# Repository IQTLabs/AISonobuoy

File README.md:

[contributors-shield]: https://img.shields.io/github/contributors/IQTLabs/edgetech-audio-recorder.svg?style=for-the-badge
[contributors-url]: https://github.com/IQTLabs/edgetech-audio-recorder/graphs/contributors
[forks-shield]: https://img.shields.io/github/forks/IQTLabs/edgetech-audio-recorder.svg?style=for-the-badge
[forks-url]: https://github.com/IQTLabs/edgetech-audio-recorder/network/members
[stars-shield]: https://img.shields.io/github/stars/IQTLabs/edgetech-audio-recorder.svg?style=for-the-badge
[stars-url]: https://github.com/IQTLabs/edgetech-audio-recorder/stargazers
[issues-shield]: https://img.shields.io/github/issues/IQTLabs/edgetech-audio-recorder.svg?style=for-the-badge
[issues-url]: https://github.com/IQTLabs/edgetech-audio-recorder/issues
[license-shield]: https://img.shields.io/github/license/IQTLabs/edgetech-audio-recorder.svg?style=for-the-badge
[license-url]: https://github.com/IQTLabs/edgetech-audio-recorder/blob/master/LICENSE.txt
[product-screenshot]: images/screenshot.png

[Python]: https://img.shields.io/badge/python-000000?style=for-the-badge&logo=python
[Python-url]: https://www.python.org
[Poetry]: https://img.shields.io/badge/poetry-20232A?style=for-the-badge&logo=poetry
[Poetry-url]: https://python-poetry.org
[Docker]: https://img.shields.io/badge/docker-35495E?style=for-the-badge&logo=docker
[Docker-url]: https://www.docker.com

[![Contributors][contributors-shield]][contributors-url]
[![Forks][forks-shield]][forks-url]
[![Stargazers][stars-shield]][stars-url]
[![Issues][issues-shield]][issues-url]
[![MIT License][license-shield]][license-url]

<br />
<div align="center">

<h1 align="center">AISonobuoy</h1>

  <p align="center"> 
    <br/>
    <br/>
    <a href="https://github.com/IQTLabs/AISonobuoy/pulls">Make Contribution</a>
    ·
    <a href="https://github.com/IQTLabs/AISonobuoy/issues">Report Bug</a>
    ·
    <a href="https://github.com/IQTLabs/AISonobuoy/issues">Request Feature</a>
  </p>
</div>

## About

## Getting Started

## Software

### Running

#### Prerequisites

## Machine Learning

### Running

#### Prerequisites

### Development

## Hardware

### BOM

### 3D Printed STL Files

### Assembly Animation (Coming soon...)

## Roadmap

## Contributing

1. Fork the Project
2. Create your Feature Branch (`git checkout -b dev`)
3. Commit your Changes (`git commit -m 'adding some feature'`)
5. Push to the Branch (`git push origin dev`)
6. Open a Pull Request

See `CONTRIBUTING.md` for more information.

## License

Distributed under the [Apache 2.0](https://github.com/IQTLabs/aisonobuoy-collector-pinephone/blob/main/LICENSE). See `LICENSE` for more information.

## Contact IQTLabs

  - Twtiter: [@iqtlabs](https://twitter.com/iqtlabs)
  - Email: info@iqtlabs.org

See our other projects: [https://github.com/IQTLabs/](https://github.com/IQTLabs/)

<p align="right">(<a href="#readme-top">back to top</a>)</p>

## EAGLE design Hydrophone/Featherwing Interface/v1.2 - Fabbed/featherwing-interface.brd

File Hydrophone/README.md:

# TinyML & Hydrophones

## What are these things?

This is a small effort to look at running ML models against Hydrophone data on an Arduino or similar microcontroller. TinyML focuses on getting machine learning working on these lower power devices. New tools, like [Edge Impulse](https://www.edgeimpulse.com), have made it easy to start building your own ML models. 

Hydrophones are microphones that can capture underwater sounds. You will often see them in movies where they are hunting submarines. There are lots of interesting things you can hear underwater, like fish, volcanos and boats. 

Being able to push audio from a hydrophone through a TinyML model would make it possible to build a self-contained sensor that could detect underwater events.

## What is this?

This work was put together to see if it is possible to detect underwater events on an Arduino. It includes a board for connecting a hydrophone to a microntroller and a small Arduino program that runs an ML model and displays whether a boat was detected.

### Hydrophone Interface Board

This is a Featherwing form factor board that has a 3.5mm jack, a MAX4466 chip and adjustable gain. It outputs the amplified audio out on one of the Feather analog pinouts. There is a short step-by-step walk through on how I built the board on [Hackster.io](https://www.hackster.io/robotastic/hydrophone-feather-board-03f1d7).

I used the following parts. I am not an EE, so feel free to pick more appropriate components (and send me a PR if you do!):
- [Adafruit PyBadge](https://www.adafruit.com/product/4200)
- [Capacitor 0.01uF / 10000pF 0805](https://www.digikey.com/en/products/detail/CL21C103JBFNNNG/1276-6487-1-ND/5958115?itemSeq=376128529)
- [Capacitor 10uF 0805](https://www.digikey.com/short/m8wb1vc5)
- [Capacitor 100pF 0805](https://www.digikey.com/short/bvph8r4p)
- [Capacitor 0.1uF 0805](https://www.digikey.com/short/ftrt382h)
- [Ferrite Bead 0805](https://www.digikey.com/short/7c5j278m)
- [3.5mm Monojack](https://www.digikey.com/short/59mz8349)
- [Resistor 1k ohm 0805](https://www.digikey.com/short/q990d7bq)
- [Resistor 1M ohm 0805](https://www.digikey.com/short/53rz9h3m)
- [Resistor 22K ohm 0805](https://www.digikey.com/short/hj1djmt8)
- [MAX4466EXK+T  SC-70-5](https://www.digikey.com/short/vnww7j39)
- [Featherwing Male Headers](https://www.adafruit.com/product/3002) 

Here is a short journey on how the board came to be:

I selected the Aquarian hydrophone to work with. The [H2A model](https://www.aquarianaudio.com/h2a-hydrophone.html) seemed to be rugged and reasonably priced, for a hydrophone. It uses a standard 3.5mm jack, making it easy to connect to a lot of different recorders. 

I haven't worked much with microphones before, so I learned a number of things. First, microphones need a bit of power to work, so they will not work on a "line-in" input. For interfacing with an Arduino, this means that you can not simply hook it up to a GPIO pin and read the signal. You need to put some power through the microphone. Secondly, the actual signal from a microphone is quite faints and needs to be amplified before you can start to work with. 

The good news is that there are lots of existing chips for working with microphones that handle both the power and the gain. The surprising thing though, was that I couldn't find an existing board that had a 3.5mm jack and was designed to be connected to an Arduino. In fact, there wasn't really that much information about recording analog audio, directly from a microphone using Arduino. Most of the microphone breakout boards I found were for MEMS style microphones and most of them put out a digital signal. 

Adafruit does have a nice [breakout board](https://www.adafruit.com/product/1063) that uses a MAX4466 chip to power and amplify a Electret  Microphone. This is a similar type of microphone as the one inside the hydrophone. Adafruit also published a nice [guide](https://learn.adafruit.com/tensorflow-lite-for-edgebadge-kit-quickstart/assembly) on how to connect this microphone to one of their [dev boards](https://www.adafruit.com/product/4200) and how to run a TinyML model against that audio. Sampling the audio is a bit of a brute force approach - you simply set an interrupt and sample the pin at a set interval. As a quick experiment, I removed the microphone from the breakout board, added a 3.5mm jack and was able to record audio from the hydrophone.

One of the great things about Adafruit is that they open source all of their hardware designs. I started with the design files for the Electret Mic Breakout Board, moved them around to fit inside the feather form factor and added a 3.5mm jack.

The resulting board fits nicely on the back of the PyBadge and will work with the large range of dev boards that are in the Feather form factor.

Unfortunately, the audio from the interface board is not as high quality as audio recorded from a digital recorder (Zoom H1n). In order to evaluate performance I used an underwater speaker to playback an audio clip. I placed both the microphone and hydrophone in bucket, to try and make it a little more realistic. 

- [Interface Board](media/FeatherWing-Audio-Test.wav)
- [Digital Recorder](media/Digital-Recorder.wav)

As you can hear, the audio recorded by the interface board is a little more muffled and has more noise than the audio recorded by the digital recorder. (It is a little jumpy because it is recorded in 1 second segments.)

The difference maybe from the sampling technique used to capture the audio, it is only 12-bits. It is more likely from the design of the interface board. Cleaning amplifying audio is an art... and I am not an artist. Any improvements to the design of the interface board would be greatly appreciated.

### Arduino Program

The Arduino program builds off of the example Arduino program from Edge Impulse for inferencing. It is designed to run on the Adafruit [Pybadge](https://www.adafruit.com/product/4200) or Edge Badge. These are a series of development boards with a SAMD51 Cortex M4F processor and a small TFT LCD screen. 

The example program is written to pull audio from a PDM microphone. I updated it to instead sample from an analog pin. The results of running the model on the audio are displayed on the screen, along with the waveform of the audio. It makes for a compact kit for debugging and evaluating model performance in the field.

## Building an ML Based Boat Detector

Generally, the first step in building an ML model is to collect data and label it. For boat detection, I wanted recordings where there was a boat going by in the water and also recordings where there are no boats present. I captured the recordings using a [Zoom H1n recorder](https://zoomcorp.com/en/us/handheld-recorders/handheld-recorders/h1n-handy-recorder/) and the Acquarian hydrophone. In addition to not being an audio expert, I am also not a boating expert. I learned a couple lessons about boats by trying to make these recordings:

1. Just because a boat is docked and not moving, doesn't mean that it is making boat sounds. It turns out that a pump and maybe a motor will be running even if the boat is docked. This means that it is a bad idea to try and record near a marina, because there will be a lot of background boat sounds, even if nothing is moving nearby.
1. Boats can sound very different. The diesel engine on the water taxi sounds a lot different that the outboard engine on a power boat.

I uploaded the different recordings to Edge Impulse and trained a model. They have recently added an AutoML feature to the platform and using that I was able to train a model that almost perfectly classified each type of audio. This is encouraging, but also suggests that I may need more audio and more variety.

## Results 
I did some field evaluation and the system is able to detect nearby boats. More testing is need to see how it would perform in different bodies of water besides a river. Additional training data should help improve performance and allow the model to generalize to a broader range of boats and conditions. Improvements to the interface board should also improve performance.

An Arduino library that includes this model is included. I will look to added the recorded audio to the repo in the future.

## Contact

If you have questions or advice, please reach out to me (Luke Berndt) -> lberndt@iqt.org

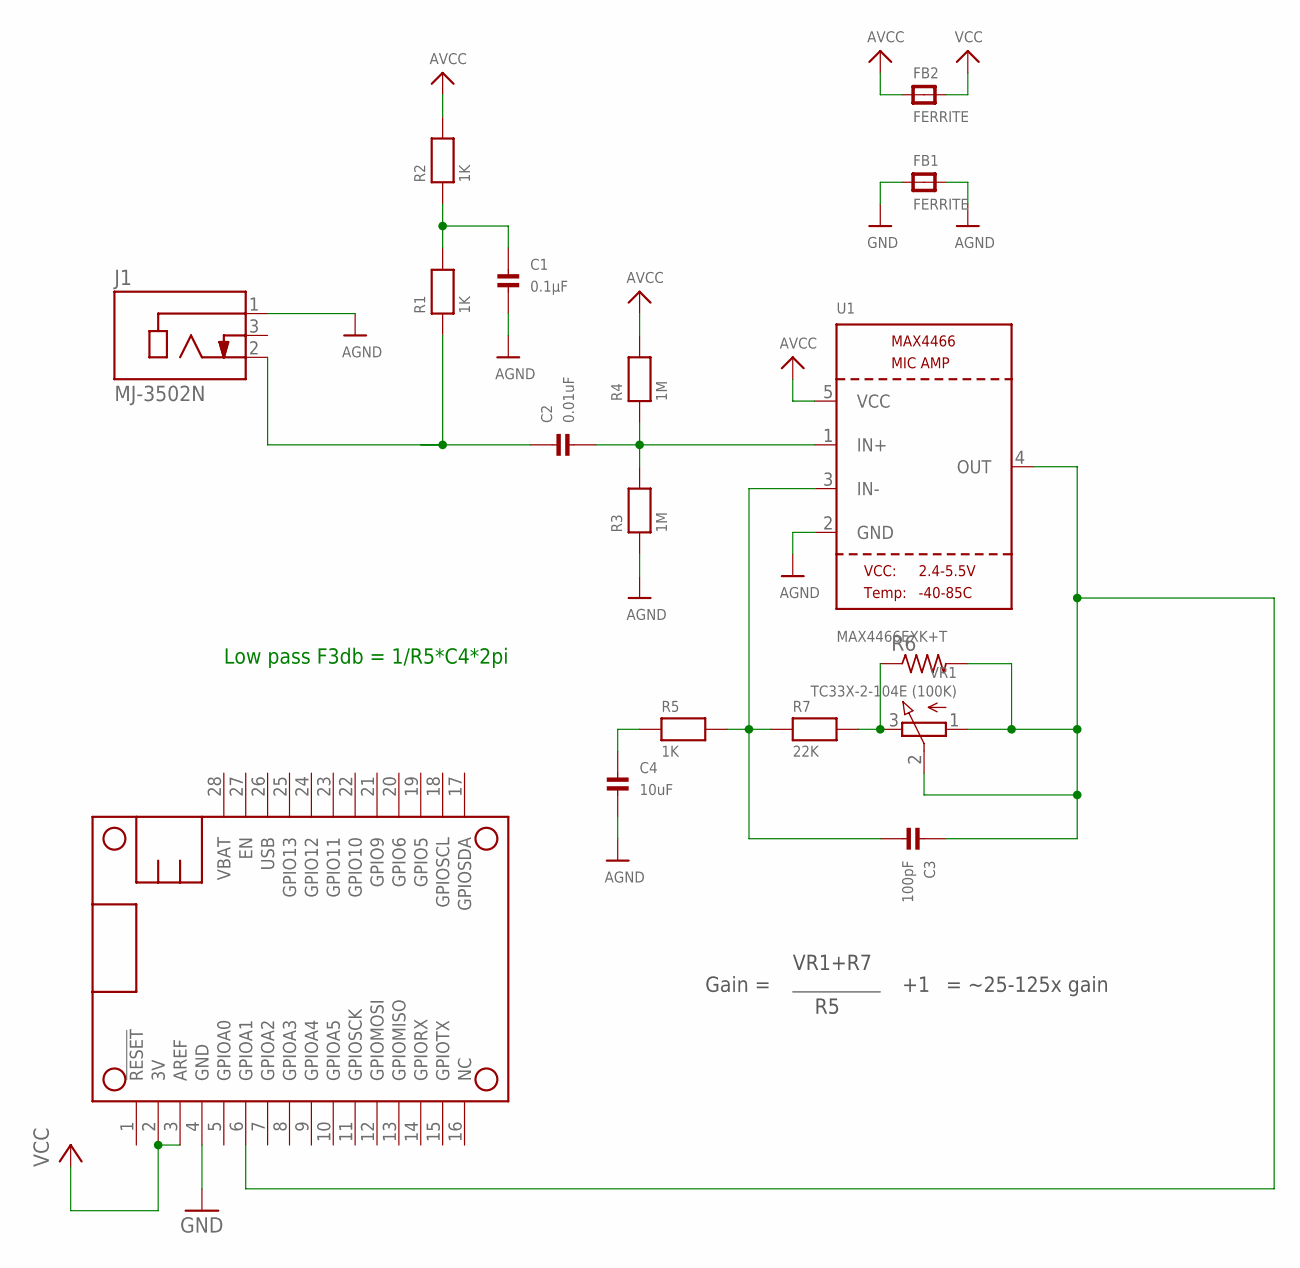
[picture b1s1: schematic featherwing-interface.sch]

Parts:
C1: 0.1µF; 0805
C2: 0.01uF; 0805
C3: 100pF; 0805
C4: 10uF; 0805
FB1, FB2: FERRITE; 0805
J1: MJ-3502N; CUI_MJ-3502N
MS1: FEATHERWING
R1, R2, R5: 1K; 0805
R3, R4: 1M; 0805
R6: R-US_0207/10; 0207/10
R7: 22K; 0805
U1: MAX4466EXK+T; SC70-5
VR1: TC33X-2-104E (100K); TRIMPOT_BOURNS_TC33X-2

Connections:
AGND: C1.2, C4.2, FB1.2, J1.1, R3.1, U1.2 (GND)
AVCC: FB2.1, R2.2, R4.2, U1.5 (VCC)
GND: FB1.1, MS1.4 (GND)
unnamed: C3.2, R5.2, R7.1, U1.3 (IN-)
unnamed: R6.1, R7.2, VR1.3 (E)
unnamed: C2.1, J1.2, R1.1
unnamed: C1.1, R1.2, R2.1
unnamed: C2.2, R3.2, R4.1, U1.1 (IN+)
unnamed: C3.1, MS1.6 (GPIOA1), R6.2, U1.4 (OUT), VR1.1 (A), VR1.2 (S)
unnamed: C4.1, R5.1
VCC: FB2.2, MS1.2 (3V), MS1.3 (AREF)

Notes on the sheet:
Gain =
VR1+R7
= ~25-125x gain
Low pass F3db = 1/R5*C4*2pi

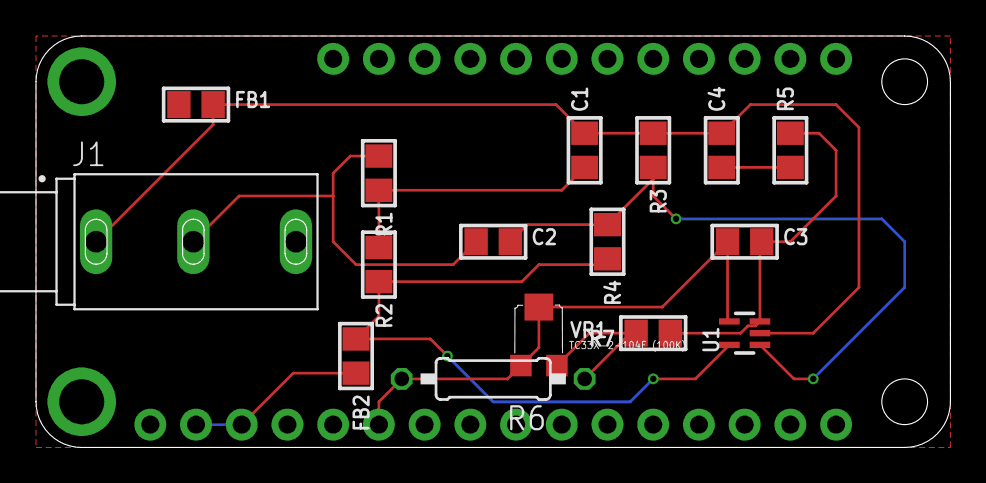
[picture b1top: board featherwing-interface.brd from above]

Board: 2 copper layers, 50.8 x 22.9 mm, 17 parts (0 on the bottom side), 11 nets.

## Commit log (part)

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2022-07-06 Upgrade requirements
2022-07-06 Update actions/checkout action to v3
2022-07-11 Create and use split_parquet method for testing
2022-07-11 Add ais-fixed.parquet
2022-07-11 Change type on test fixture
2022-07-12 Remove a test as a test
2022-07-12 Remove augmented fields as a test
2022-07-12 Testing only integers as a test
2022-07-12 Compare distance and speed to within a threshold
2022-07-12 Change float comparison to relative from absolute
2022-07-12 Minor comment change
2022-07-12 Attempt to resolve static code analysis issues
2022-07-12 Resolve static code analysis issues
2022-07-12 Try yet again to resolve static code analysis issue
2022-07-12 Remove bandit configuration since it is set on the codacy side
2022-07-13 Update test and add DataScience workflow (#854)
    * Add workflow and fix test paths
    * Upgrade requirements
    * Upgrade requirements
    * Upgrade requirements
    * Create and use split_parquet method for testing
    * Update test workflow
2022-07-14 Update dependency pyais to v2
2022-07-15 Update actions/setup-python action to v4
2022-07-18 Refresh pip-compile outputs
2022-07-18 Update boto packages
2022-07-20 Fix pyais version
2022-07-20 Add a package rule (#879)
    * Update dependency jsonschema to v4.7.2
    * Update dependency nbclassic to v0.4.3
    * Update dependency zipp to v3.8.1
    * Update dependency pyais to v2
    * Update dependency awscli to v1.25.30
    * Update dependency boto3 to v1.24.30
2022-07-22 Update dependency awscli to v1.25.35 (#882)
2022-07-25 updated graphing code
2022-07-25 codacy formatting cleanup
2022-07-27 Update Update dependency botocore and boto3
2022-07-28 Update group name for boto package rule
2022-07-29 formatting 2
2022-07-29 cleanup
2022-08-02 Update dependency attrs to v22
2022-08-11 Update dependency pyarrow to v9
2022-08-12 Update dependency mistune to v2 [SECURITY]
2022-08-31 Update dependency docker to v6
2022-08-31 fix more paths for pytype
2022-08-31 comment edits
2022-09-01 revised testing scripts
2022-09-01 missed a zero length test
2022-09-02 review revisions
2022-09-22 Update actions/stale action to v6
2022-09-28 inital torch modeling pipeline + cleanup
2022-10-02 training loop + minor edits
2022-10-04 documentation v1
2022-10-05 Correct spelling errors
2022-10-06 add torch -> ONNX -> keras -> tflite conversion
2022-10-06 fix semgrep Python errors
2022-10-11 adding clustering pipeline
2022-10-14 rnd 1 codacity updates
2022-10-14 rnd 2 codacity updates
2022-10-14 rnd 4 codacity updates
2022-10-17 codacity rnd 5
2022-10-17 adding clustering scripts
2022-10-17 renaming directory
2022-10-17 codacity rnd 1 updates
2022-10-18 Bump joblib from 1.1.0 to 1.2.0 in /DataScience/modeling
    Bumps [joblib](https://github.com/joblib/joblib) from 1.1.0 to 1.2.0.
    - [Release notes](https://github.com/joblib/joblib/releases)
    - [Changelog](https://github.com/joblib/joblib/blob/master/CHANGES.rst)
    - [Commits](https://github.com/joblib/joblib/compare/1.1.0...1.2.0)
    ---
    updated-dependencies:
2022-10-18 Bump nbconvert from 6.5.0 to 6.5.1 in /DataScience/modeling
    Bumps [nbconvert](https://github.com/jupyter/nbconvert) from 6.5.0 to 6.5.1.
    - [Release notes](https://github.com/jupyter/nbconvert/releases)
    - [Changelog](https://github.com/jupyter/nbconvert/blob/main/CHANGELOG.md)
    - [Commits](https://github.com/jupyter/nbconvert/compare/6.5...6.5.1)
    ---
    updated-dependencies:
2022-10-18 updating requirements file
2022-10-18 Bump protobuf from 3.9.2 to 3.18.3 in /DataScience/cnn_modeling
    Bumps [protobuf](https://github.com/protocolbuffers/protobuf) from 3.9.2 to 3.18.3.
    - [Release notes](https://github.com/protocolbuffers/protobuf/releases)
    - [Changelog](https://github.com/protocolbuffers/protobuf/blob/main/generate_changelog.py)
    - [Commits](https://github.com/protocolbuffers/protobuf/compare/v3.9.2...v3.18.3)
    ---
    updated-dependencies:
2022-10-18 Bump joblib from 1.1.0 to 1.2.0 in /DataScience/cnn_modeling
    Bumps [joblib](https://github.com/joblib/joblib) from 1.1.0 to 1.2.0.
    - [Release notes](https://github.com/joblib/joblib/releases)
    - [Changelog](https://github.com/joblib/joblib/blob/master/CHANGES.rst)
    - [Commits](https://github.com/joblib/joblib/compare/1.1.0...1.2.0)
    ---
    updated-dependencies:
2022-10-18 Update dependency nbconvert to v6.5.1 [SECURITY]
2022-10-18 Update dependency protobuf to v3.18.3 [SECURITY]
2022-10-19 updating renovate ignore files:
2022-10-22 updating cnn modeling requirements
2022-10-22 updating clustering requirements
2022-12-09 Clean up from Raspberry Pi buoy transfer
2022-12-09 Update pibuoy README links
2023-01-10 Skip files not ending in .json
2023-01-10 Exclude AIS sample dictionary keys that are not needed
2023-01-10 Add a mutually exclusive options to skip or force downloading
2023-01-12 Do not raise an exception when not finding an interval
    And add a TODO to understand why the interval isn't found
2023-01-13 Blacken buffer and format
2023-01-13 Add functions to compute source level
2023-01-13 Add entries for computing source level
2023-01-13 Add data for testing computation of source level
2023-01-13 Update test data to remove 'radio' key
2023-01-20 Plot power spectral densities for specified ship types
2023-01-20 Add a test of the PSD computation
2023-01-20 Ignore additional return values
2023-01-23 Downsample pressure for plotting
2023-01-23 Add method for writing SLs, and update plotting of pressure time series, and pressure spectral densities
2023-02-02 Update actions/stale action to v7
2023-02-03 remove legacy experiments
2023-03-27 add security policy
2023-03-27 add code of conduct
2023-03-30 Update actions/stale action to v8
2023-09-05 Update actions/checkout action to v4
2023-09-13 Update docker/setup-qemu-action action to v3
2023-11-03 Bump pillow from 9.2.0 to 10.0.1 in /DataScience/cnn_modeling
    Bumps [pillow](https://github.com/python-pillow/Pillow) from 9.2.0 to 10.0.1.
    - [Release notes](https://github.com/python-pillow/Pillow/releases)
    - [Changelog](https://github.com/python-pillow/Pillow/blob/main/CHANGES.rst)
    - [Commits](https://github.com/python-pillow/Pillow/compare/9.2.0...10.0.1)
    ---
    updated-dependencies:
2023-11-09 Bump pyarrow from 9.0.0 to 14.0.1 in /DataScience
    Bumps [pyarrow](https://github.com/apache/arrow) from 9.0.0 to 14.0.1.
    - [Commits](https://github.com/apache/arrow/compare/go/v9.0.0...apache-arrow-14.0.1)
    ---
    updated-dependencies:
    - dependency-name: pyarrow
    dependency-type: direct:production
2023-11-14 Update actions/github-script action to v7
2023-12-07 Update actions/setup-python action to v5
2024-01-09 Bump fonttools from 4.34.4 to 4.43.0 in /DataScience/cnn_modeling
    Bumps [fonttools](https://github.com/fonttools/fonttools) from 4.34.4 to 4.43.0.
    - [Release notes](https://github.com/fonttools/fonttools/releases)
    - [Changelog](https://github.com/fonttools/fonttools/blob/main/NEWS.rst)
    - [Commits](https://github.com/fonttools/fonttools/compare/4.34.4...4.43.0)
    ---
    updated-dependencies:
2024-01-11 Bump jinja2 from 3.1.2 to 3.1.3 in /DataScience
    Bumps [jinja2](https://github.com/pallets/jinja) from 3.1.2 to 3.1.3.
    - [Release notes](https://github.com/pallets/jinja/releases)
    - [Changelog](https://github.com/pallets/jinja/blob/main/CHANGES.rst)
    - [Commits](https://github.com/pallets/jinja/compare/3.1.2...3.1.3)
    ---
    updated-dependencies:
2024-01-23 Bump pillow from 9.2.0 to 10.2.0 in /DataScience/cnn_modeling
    Bumps [pillow](https://github.com/python-pillow/Pillow) from 9.2.0 to 10.2.0.
    - [Release notes](https://github.com/python-pillow/Pillow/releases)
    - [Changelog](https://github.com/python-pillow/Pillow/blob/main/CHANGES.rst)
    - [Commits](https://github.com/python-pillow/Pillow/compare/9.2.0...10.2.0)
    ---
    updated-dependencies:
2024-01-23 Bump pillow from 9.2.0 to 10.2.0 in /DataScience/clustering_modeling
    Bumps [pillow](https://github.com/python-pillow/Pillow) from 9.2.0 to 10.2.0.
    - [Release notes](https://github.com/python-pillow/Pillow/releases)
    - [Changelog](https://github.com/python-pillow/Pillow/blob/main/CHANGES.rst)
    - [Commits](https://github.com/python-pillow/Pillow/compare/9.2.0...10.2.0)
    ---
    updated-dependencies:
2024-03-26 Update codecov/codecov-action action to v4
2024-04-03 Bump pillow from 9.2.0 to 10.3.0 in /DataScience/cnn_modeling
    Bumps [pillow](https://github.com/python-pillow/Pillow) from 9.2.0 to 10.3.0.
    - [Release notes](https://github.com/python-pillow/Pillow/releases)
    - [Changelog](https://github.com/python-pillow/Pillow/blob/main/CHANGES.rst)
    - [Commits](https://github.com/python-pillow/Pillow/compare/9.2.0...10.3.0)
    ---
    updated-dependencies:
2024-04-12 Bump idna from 3.4 to 3.7 in /DataScience/clustering_modeling
    Bumps [idna](https://github.com/kjd/idna) from 3.4 to 3.7.
    - [Release notes](https://github.com/kjd/idna/releases)
    - [Changelog](https://github.com/kjd/idna/blob/master/HISTORY.rst)
    - [Commits](https://github.com/kjd/idna/compare/v3.4...v3.7)
    ---
    updated-dependencies:
2024-05-06 Bump werkzeug from 2.2.0 to 3.0.3 in /DataScience/cnn_modeling
    Bumps [werkzeug](https://github.com/pallets/werkzeug) from 2.2.0 to 3.0.3.
    - [Release notes](https://github.com/pallets/werkzeug/releases)
    - [Changelog](https://github.com/pallets/werkzeug/blob/main/CHANGES.rst)
    - [Commits](https://github.com/pallets/werkzeug/compare/2.2.0...3.0.3)
    ---
    updated-dependencies:
2024-05-21 --- updated-dependencies: - dependency-name: requests dependency-type: indirect ...
2024-08-29 Bump jupyterlab from 3.4.8 to 3.6.8 in /DataScience
    Bumps [jupyterlab](https://github.com/jupyterlab/jupyterlab) from 3.4.8 to 3.6.8.
    - [Release notes](https://github.com/jupyterlab/jupyterlab/releases)
    - [Changelog](https://github.com/jupyterlab/jupyterlab/blob/main/CHANGELOG.md)
    - [Commits](https://github.com/jupyterlab/jupyterlab/compare/@jupyterlab/vdom@3.4.8...@jupyterlab/vdom@3.6.8)
    ---
    updated-dependencies:
2024-10-25 Bump werkzeug from 2.2.0 to 3.0.6 in /DataScience/cnn_modeling
    Bumps [werkzeug](https://github.com/pallets/werkzeug) from 2.2.0 to 3.0.6.
    - [Release notes](https://github.com/pallets/werkzeug/releases)
    - [Changelog](https://github.com/pallets/werkzeug/blob/main/CHANGES.rst)
    - [Commits](https://github.com/pallets/werkzeug/compare/2.2.0...3.0.6)
    ---
    updated-dependencies:
2024-11-19 Bump wheel from 0.37.1 to 0.38.1 in /DataScience/cnn_modeling
    Bumps [wheel](https://github.com/pypa/wheel) from 0.37.1 to 0.38.1.
    - [Release notes](https://github.com/pypa/wheel/releases)
    - [Changelog](https://github.com/pypa/wheel/blob/main/docs/news.rst)
    - [Commits](https://github.com/pypa/wheel/compare/0.37.1...0.38.1)
    ---
    updated-dependencies:
2024-12-23 Bump jinja2 from 3.1.2 to 3.1.5 in /DataScience
    Bumps [jinja2](https://github.com/pallets/jinja) from 3.1.2 to 3.1.5.
    - [Release notes](https://github.com/pallets/jinja/releases)
    - [Changelog](https://github.com/pallets/jinja/blob/main/CHANGES.rst)
    - [Commits](https://github.com/pallets/jinja/compare/3.1.2...3.1.5)
    ---
    updated-dependencies:
2025-03-06 Bump jinja2 from 3.1.2 to 3.1.6 in /DataScience
    Bumps [jinja2](https://github.com/pallets/jinja) from 3.1.2 to 3.1.6.
    - [Release notes](https://github.com/pallets/jinja/releases)
    - [Changelog](https://github.com/pallets/jinja/blob/main/CHANGES.rst)
    - [Commits](https://github.com/pallets/jinja/compare/3.1.2...3.1.6)
    ---
    updated-dependencies:

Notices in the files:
parts and their libraries:
microbuilder: This work is placed in the public domain, and may be freely used for commercial and non-commercial work with the following conditions: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
